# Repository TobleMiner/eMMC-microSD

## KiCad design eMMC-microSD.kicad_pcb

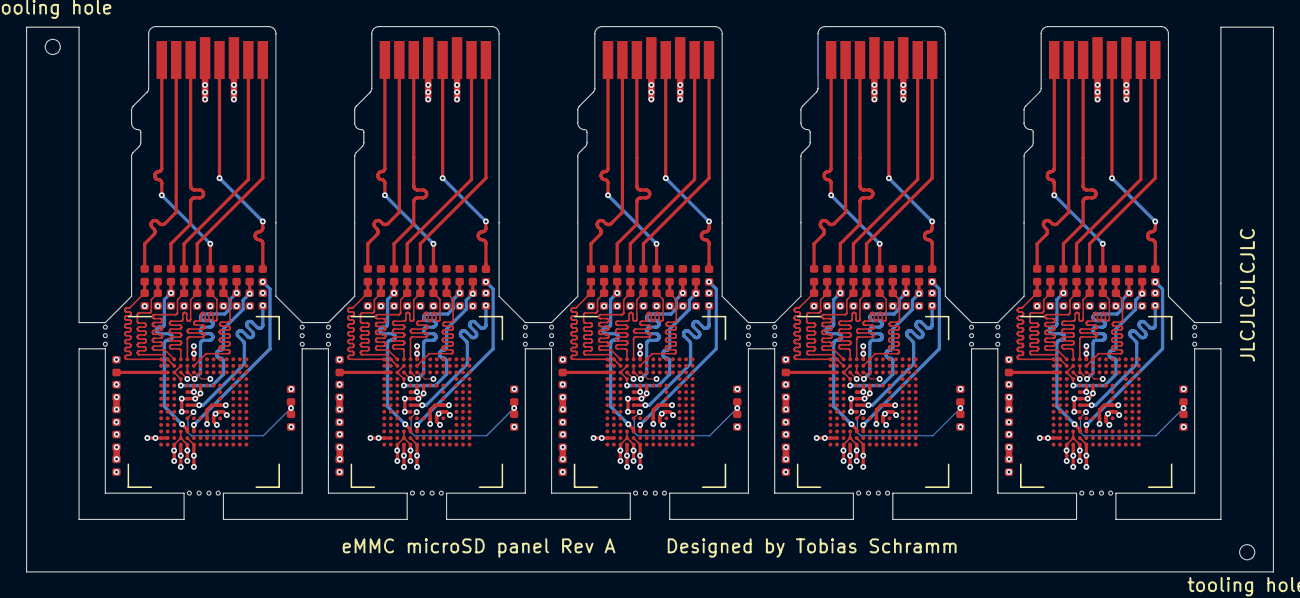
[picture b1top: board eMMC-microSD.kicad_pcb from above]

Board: 4 copper layers, 95.0 x 41.5 mm, 197 parts (0 on the bottom side), 97 nets.

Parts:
C1, C2, C3, C6, C7, C8, C9, C12, C13, C14, C15, C18, C19, C20, C21, C24, C25, C26, C27, C30: 100nF; C_0402_1005Metric
C4, C5, C10, C11, C16, C17, C22, C23, C28, C29: 4.7uF; C_0402_1005Metric
H1, H2: MountingHole; ToolingHole_JLCSMT
H3, H4, H5, H6, H7, H8, H9, H10, H11, H12, H13, H14, H15, H16, H17, H18, H19, H20, H21, H22, H23, H24, H25, H26, H27, H28, H29, H30, H31, H32, H33, H34, H35, H36, H37, H38, H39, H40, H41, H42, H43, H44, H45, H46, H47, H48, H49, H50, H51, H52: MountingHole; Perforation_0.3mm
J1, J2, J3, J4, J5: Micro_SD_Card; Card_Edge_micro_SD_full
R1, R2, R3, R4, R5, R6, R7, R8, R9, R10, R11, R12, R13, R14, R15, R16, R17, R18, R19, R20, R21, R22, R23, R24, R25, R26, R27, R28, R29, R30, R31, R32, R33, R34, R35, R36, R37, R38, R39, R40, R41, R42, R43, R44, R45, R46, R47, R48, R49, R50, R101, R102, R103, R104, R105: 10kR; R_0402_1005Metric
R51, R52, R53, R54, R55, R56, R57, R58, R59, R60, R61, R62, R63, R64, R65, R66, R67, R68, R69, R70, R71, R72, R73, R74, R75, R76, R77, R78, R79, R80, R81, R82, R83, R84, R85, R86, R87, R88, R89, R90, R91, R92, R93, R94, R95, R96, R97, R98, R99, R100: 33R; R_0402_1005Metric
U1, U2, U3, U4, U5: eMMC_5.1_BGA153; eMMC-FBGA-153

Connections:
/Adapter 1/CLK: J1.5, R60.2
/Adapter 1/CMD: J1.3, R53.2
/Adapter 1/D3: R11.2, R58.1, U1.A1, U1.B2
/Adapter 1/D4: R10.2, R55.1, U1.A2, U1.B3
/Adapter 1/D5: R9.2, R52.1, U1.B4, U1.C3, U1.D4
/Adapter 1/D6: R8.2, R59.1, U1.B5, U1.C5
/Adapter 1/D7: R7.2, R56.1, U1.A7, U1.B6
/Adapter 1/DAT0: J1.7, R57.2
/Adapter 1/DAT1: J1.8, R54.2
/Adapter 1/DAT2: J1.1, R51.2
/Adapter 1/DAT3: J1.2, R58.2
/Adapter 2/CLK: J2.5, R70.2
/Adapter 2/CMD: J2.3, R63.2
/Adapter 2/D3: R20.2, R68.1, U2.A1, U2.B2
/Adapter 2/D4: R19.2, R65.1, U2.A2, U2.B3
/Adapter 2/D5: R18.2, R62.1, U2.B4, U2.C3, U2.D4
/Adapter 2/D6: R17.2, R69.1, U2.B5, U2.C5
/Adapter 2/D7: R16.2, R66.1, U2.A7, U2.B6
/Adapter 2/DAT0: J2.7, R67.2
/Adapter 2/DAT1: J2.8, R64.2
/Adapter 2/DAT2: J2.1, R61.2
/Adapter 2/DAT3: J2.2, R68.2
/Adapter 3/CLK: J3.5, R80.2
/Adapter 3/CMD: J3.3, R73.2
/Adapter 3/D3: R29.2, R78.1, U3.A1, U3.B2
/Adapter 3/D4: R28.2, R75.1, U3.A2, U3.B3
/Adapter 3/D5: R27.2, R72.1, U3.B4, U3.C3, U3.D4
/Adapter 3/D6: R26.2, R79.1, U3.B5, U3.C5
/Adapter 3/D7: R25.2, R76.1, U3.A7, U3.B6
/Adapter 3/DAT0: J3.7, R77.2
/Adapter 3/DAT1: J3.8, R74.2
/Adapter 3/DAT2: J3.1, R71.2
/Adapter 3/DAT3: J3.2, R78.2
/Adapter 4/CLK: J4.5, R90.2
/Adapter 4/CMD: J4.3, R83.2
/Adapter 4/D3: R38.2, R88.1, U4.A1, U4.B2
/Adapter 4/D4: R37.2, R85.1, U4.A2, U4.B3
/Adapter 4/D5: R36.2, R82.1, U4.B4, U4.C3, U4.D4
/Adapter 4/D6: R35.2, R89.1, U4.B5, U4.C5
/Adapter 4/D7: R34.2, R86.1, U4.A7, U4.B6
/Adapter 4/DAT0: J4.7, R87.2
/Adapter 4/DAT1: J4.8, R84.2
/Adapter 4/DAT2: J4.1, R81.2
/Adapter 4/DAT3: J4.2, R88.2
/Adapter 5/CLK: J5.5, R100.2
/Adapter 5/CMD: J5.3, R93.2
/Adapter 5/D3: R47.2, R98.1, U5.A1, U5.B2
/Adapter 5/D4: R46.2, R95.1, U5.A2, U5.B3
/Adapter 5/D5: R45.2, R92.1, U5.B4, U5.C3, U5.D4
/Adapter 5/D6: R44.2, R99.1, U5.B5, U5.C5
/Adapter 5/D7: R43.2, R96.1, U5.A7, U5.B6
/Adapter 5/DAT0: J5.7, R97.2
/Adapter 5/DAT1: J5.8, R94.2
/Adapter 5/DAT2: J5.1, R91.2
/Adapter 5/DAT3: J5.2, R98.2
GND: C1.1, C2.2, C3.2, C4.2, C5.2, C6.2, C7.1, C8.2, C9.2, C10.2, C11.2, C12.2, C13.1, C14.2, C15.2, C16.2, C17.2, C18.2, C19.1, C20.2, C21.2, C22.2, C23.2, C24.2, C25.1, C26.2, C27.2, C28.2, C29.2, C30.2, J1.6, J2.6, J3.6, J4.6, J5.6, R101.2, R102.2, R103.2, R104.2, R105.2, U1.A6, U1.C4, U1.E7, U1.G5, U1.H10, U1.J5, U1.K8, U1.N2, U1.N5, U1.P4, U1.P6, U2.A6, U2.C4, U2.E7, U2.G5, U2.H10, U2.J5, U2.K8, U2.N2, U2.N5, U2.P4, U2.P6, U3.A6, U3.C4, U3.E7, U3.G5, U3.H10, U3.J5, U3.K8, U3.N2, U3.N5, U3.P4, U3.P6, U4.A6, U4.C4, U4.E7, U4.G5, U4.H10, U4.J5, U4.K8, U4.N2, U4.N5, U4.P4, U4.P6, U5.A6, U5.C4, U5.E7, U5.G5, U5.H10, U5.J5, U5.K8, U5.N2, U5.N5, U5.P4, U5.P6
unnamed: C1.2, R1.2, U1.K5
unnamed: C2.1, U1.C2
unnamed: C7.2, R2.2, U2.K5
unnamed: C8.1, U2.C2
unnamed: C13.2, R3.2, U3.K5
unnamed: C14.1, U3.C2
unnamed: C19.2, R4.2, U4.K5
unnamed: C20.1, U4.C2
unnamed: C25.2, R5.2, U5.K5
unnamed: C26.1, U5.C2
unnamed: R12.2, R51.1, U1.A5
unnamed: R13.2, R54.1, U1.A4
unnamed: R14.2, R57.1, U1.A3
unnamed: R15.2, R63.1, U2.M5
unnamed: R21.2, R61.1, U2.A5
unnamed: R22.2, R64.1, U2.A4
unnamed: R23.2, R67.1, U2.A3
unnamed: R24.2, R73.1, U3.M5
unnamed: R30.2, R71.1, U3.A5
unnamed: R31.2, R74.1, U3.A4
unnamed: R32.2, R77.1, U3.A3
unnamed: R33.2, R83.1, U4.M5
unnamed: R39.2, R81.1, U4.A5
unnamed: R40.2, R84.1, U4.A4
unnamed: R41.2, R87.1, U4.A3
unnamed: R42.2, R93.1, U5.M5
unnamed: R48.2, R91.1, U5.A5
unnamed: R49.2, R94.1, U5.A4
unnamed: R50.2, R97.1, U5.A3
unnamed: R6.2, R53.1, U1.M5
unnamed: R60.1, U1.M6
unnamed: R70.1, U2.M6
unnamed: R80.1, U3.M6
unnamed: R90.1, U4.M6
unnamed: R100.1, U5.M6
unnamed: R101.1, U1.H5
unnamed: R102.1, U2.H5
unnamed: R103.1, U3.H5
unnamed: R104.1, U4.H5
unnamed: R105.1, U5.H5
VCC: C3.1, C4.1, C5.1, C6.1, C9.1, C10.1, C11.1, C12.1, C15.1, C16.1, C17.1, C18.1, C21.1, C22.1, C23.1, C24.1, C27.1, C28.1, C29.1, C30.1, J1.4, J2.4, J3.4, J4.4, J5.4, R1.1, R2.1, R3.1, R4.1, R5.1, R6.1, R7.1, R8.1, R9.1, R10.1, R11.1, R12.1, R13.1, R14.1, R15.1, R16.1, R17.1, R18.1, R19.1, R20.1, R21.1, R22.1, R23.1, R24.1, R25.1, R26.1, R27.1, R28.1, R29.1, R30.1, R31.1, R32.1, R33.1, R34.1, R35.1, R36.1, R37.1, R38.1, R39.1, R40.1, R41.1, R42.1, R43.1, R44.1, R45.1, R46.1, R47.1, R48.1, R49.1, R50.1, U1.C6, U1.E6, U1.F5, U1.J10, U1.K9, U1.M4, U1.N4, U1.P3, U1.P5, U2.C6, U2.E6, U2.F5, U2.J10, U2.K9, U2.M4, U2.N4, U2.P3, U2.P5, U3.C6, U3.E6, U3.F5, U3.J10, U3.K9, U3.M4, U3.N4, U3.P3, U3.P5, U4.C6, U4.E6, U4.F5, U4.J10, U4.K9, U4.M4, U4.N4, U4.P3, U4.P5, U5.C6, U5.E6, U5.F5, U5.J10, U5.K9, U5.M4, U5.N4, U5.P3, U5.P5

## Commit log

2020-08-03 Do eMMC layout
2020-08-03 Reorganize as sub-schematics
2020-08-03 Panelize
2020-08-08 Redo termination and layout of first module
2020-08-08 Fix incorrect D6 and D3 lengths
2020-08-08 Finalize frame layout
2020-08-08 Add mousebites to first adapter
2020-08-08 Plce remaining tooling holes
2020-08-08 Hide all references
2020-08-08 Fix silkscreen
2020-08-08 Fix missing LCSC partnumbers
